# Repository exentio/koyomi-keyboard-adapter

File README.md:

# Project Koyomi - keyboard adapter boards

Adapter boards for the Vaio P keyboard, made from the reverse engineering for
Project Koyomi, read [this blog post](https://blog.exentio.sexy/2024/04/25/project-koyomi-update-2.html)
for more.  
Consider these reference designs, you can use them in hand-wired builds, to
test other keyboard variations, or for use in your own projects!  

**⚠️ WARNING: at the moment of writing, the boards haven't been tested.**  
**I'm also planning a major redesign using the RP2354B.**

The boards come in two variants, one with the RP2040 running the QMK firmware,
and another using the RP2354A with currently no firmware (waiting for QMK
support).  
For the RP2040 board, you can find the necessary build files in the
`qmk-firmware` folder. Once the board is made and tested and all the features 
are added (the extra keys are missing), it'll be pushed to the mainstream QMK
repo.  
The only supported layout for now is the JIS (Japanese) one on the first gen
Vaio P, but it's merely a matter of reversing the matrix and changing the pins
and layouts in the QMK config as necessary.  

Since the adapter's only concern is the keyboard, a header breaks out the
following:  
+ Lid detection sensor
+ Power switch
+ Power LED
+ Charging LED
+ Standby LED
+ WiFi switch
+ WiFi LED
+ Disk activity LED
+ Scroll lock LED (due to lack of GPIOs)

The keyboard connector is made by Panasonic, and the model number is
`AXK750147G`, bear in mind that the connector can connect in both ways, check
the GND connections marked on the board, the darkest traces on the keyboard
connector lead to GND.  

---

### Forking guidelines
I hope that this design will inspire people to work on similar projects, and
that they'll be used as references to learn how to work on similar projects!  
If you want to make any contribution, you're welcome to fork and send a pull
request, as long as LLMs are not directly involved and you understand your
changes: please refer to (HUMAN.md)[https://github.com/exentio/koyomi-hdmi-lvds/blob/main/HUMAN.md], thank you.  

You're also welcome to make changes to any part of this project to implement
different design choices, without having to send a pull request; however, if
your fork takes a completely different direction from Koyomi and breaks
compatibility, I kindly ask you to drop the name "Koyomi" from your project.
Please also remove every art on the PCB, if possible (wouldn't make sense to
have my face on a completely different project anyway).  
This can't and won't be enforced, so I'm just asking informally to please
respect this request, if you want to use my designs.  

### Commercial use
I purposely decided to allow commercial use for this project for two reasons: I
would be happy if modernized Vaio Ps and Koyomi were to be used in professional
contexts, and to let people distribute PCBs so everyone can build their own,
without having to sell parts myself, which is not something I can handle.  

If you plan to sell boards and parts, I only have these simple requests:  
- Please make them reasonably affordable and don't mark them up absurdly, I
want this project to be approachable from every point of view.  
- If you're profiting from reselling my designs, please donate something back
to the people who made the designs you're selling.  
- Don't remove any drawings/art on the PCBs, but you're allowed to add your own.  

None of these can and will be enforced, so I'm just asking you to respect the
time and hard work the other contributors and I have poured into designing
Koyomi.

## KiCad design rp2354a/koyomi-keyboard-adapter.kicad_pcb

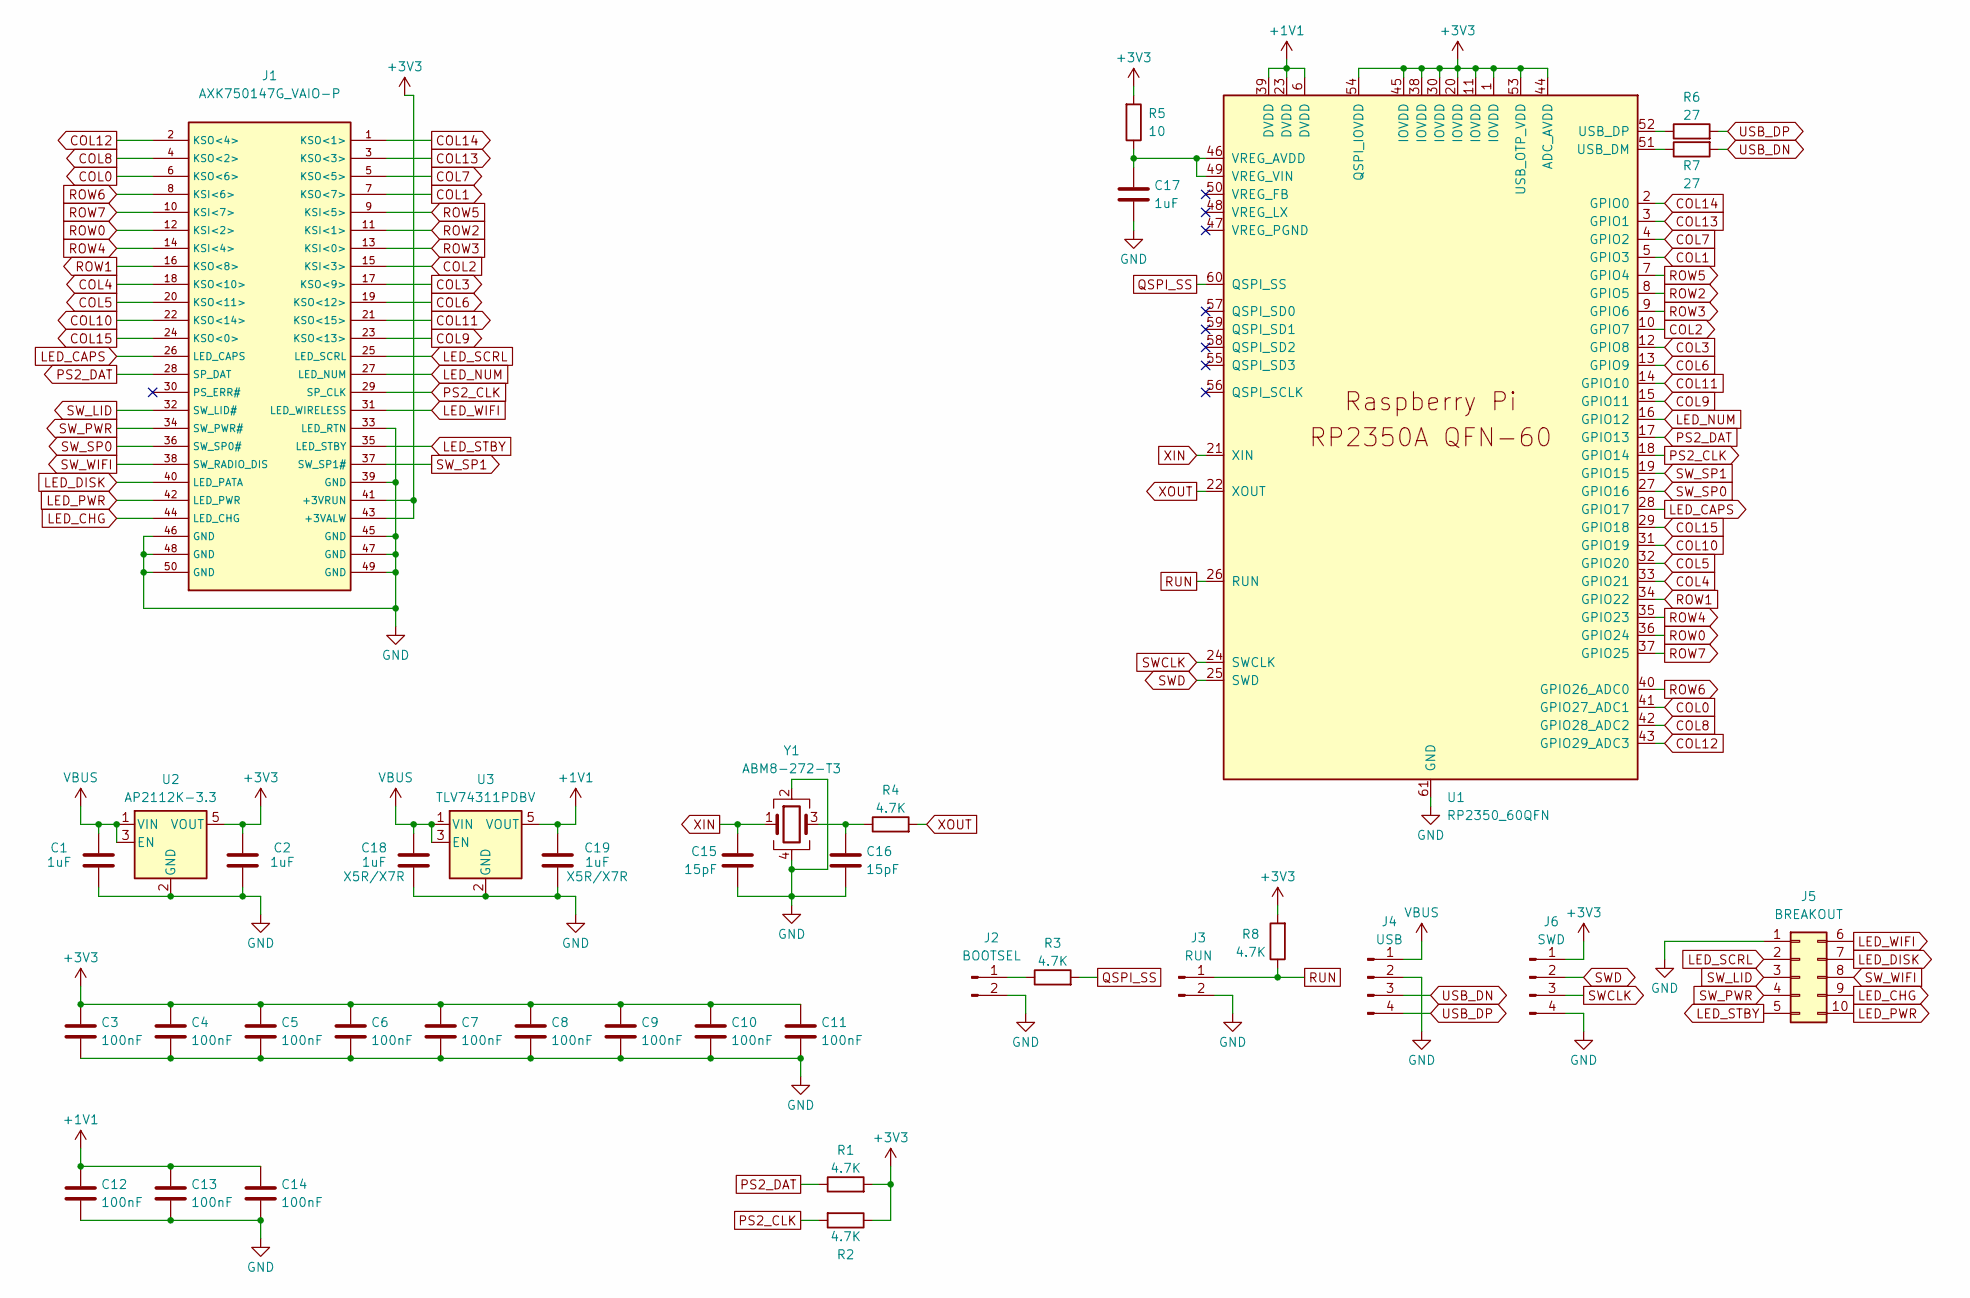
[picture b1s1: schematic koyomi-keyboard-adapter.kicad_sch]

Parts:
C1, C2, C17, C18, C19: 1uF; C_0402_1005Metric
C3, C4, C5, C6, C7, C8, C9, C10, C11, C12, C13, C14: 100nF; C_0402_1005Metric
C15, C16: 15pF; C_0402_1005Metric
J1: AXK750147G_VAIO-P
J2: BOOTSEL; PinHeader_1x02_P2.54mm_Vertical
J3: RUN; PinHeader_1x02_P2.54mm_Vertical
J4: USB; PinHeader_1x04_P2.54mm_Vertical
J5: BREAKOUT; PinHeader_2x05_P2.54mm_Vertical
J6: SWD; PinHeader_1x04_P2.54mm_Vertical
R1, R2, R3, R4, R8: 4.7K; R_0402_1005Metric
R5: 10; R_0402_1005Metric
R6, R7: 27; R_0402_1005Metric
U1: RP2350_60QFN; MCU_RaspberryPi_RP2350
U2: AP2112K-3.3; SOT-23-5
U3: TLV74311PDBV; SOT-23-5
Y1: ABM8-272-T3; Crystal_SMD_3225-4Pin_3.2x2.5mm

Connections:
+1V1: C12.1, C13.1, C14.1, C19.1, U1.6 (DVDD), U1.23 (DVDD), U1.39 (DVDD), U3.5 (VOUT)
+3V3: C2.1, C3.1, C4.1, C5.1, C6.1, C7.1, C8.1, C9.1, C10.1, C11.1, J1.41 (+3VRUN), J1.43 (+3VALW), J6.1, R1.2, R2.1, R5.2, R8.2, U1.1 (IOVDD), U1.11 (IOVDD), U1.20 (IOVDD), U1.30 (IOVDD), U1.38 (IOVDD), U1.44 (ADC_AVDD), U1.45 (IOVDD), U1.53 (USB_OTP_VDD), U1.54 (QSPI_IOVDD), U2.5 (VOUT); also elsewhere on the board
COL0: J1.6 (KSO<6>), U1.41 (GPIO27_ADC1)
COL1: J1.7 (KSO<7>), U1.5 (GPIO3)
COL2: J1.15 (KSI<3>), U1.10 (GPIO7)
COL3: J1.17 (KSO<9>), U1.12 (GPIO8)
COL4: J1.18 (KSO<10>), U1.33 (GPIO21)
COL5: J1.20 (KSO<11>), U1.32 (GPIO20)
COL6: J1.19 (KSO<12>), U1.13 (GPIO9)
COL7: J1.5 (KSO<5>), U1.4 (GPIO2)
COL8: J1.4 (KSO<2>), U1.42 (GPIO28_ADC2)
COL9: J1.23 (KSO<13>), U1.15 (GPIO11)
COL10: J1.22 (KSO<14>), U1.31 (GPIO19)
COL11: J1.21 (KSO<15>), U1.14 (GPIO10)
COL12: J1.2 (KSO<4>), U1.43 (GPIO29_ADC3)
COL13: J1.3 (KSO<3>), U1.3 (GPIO1)
COL14: J1.1 (KSO<1>), U1.2 (GPIO0)
COL15: J1.24 (KSO<0>), U1.29 (GPIO18)
GND: C1.2, C2.2, C3.2, C4.2, C5.2, C6.2, C7.2, C8.2, C9.2, C10.2, C11.2, C12.2, C13.2, C14.2, C15.2, C16.2, C17.2, C18.2, C19.2, J1.33 (LED_RTN), J1.39 (GND), J1.45 (GND), J1.46 (GND), J1.47 (GND), J1.48 (GND), J1.49 (GND), J1.50 (GND), J2.2, J3.2, J4.2, J5.1, J6.4, U1.61 (GND), U2.2 (GND), U3.2 (GND), Y1.2, Y1.4; also elsewhere on the board
LED_CAPS: J1.26 (LED_CAPS), U1.28 (GPIO17)
LED_CHG: J1.44 (LED_CHG), J5.9
LED_DISK: J1.40 (LED_PATA), J5.7
LED_NUM: J1.27 (LED_NUM), U1.16 (GPIO12)
LED_PWR: J1.42 (LED_PWR), J5.10
LED_SCRL: J1.25 (LED_SCRL), J5.2
LED_STBY: J1.35 (LED_STBY), J5.5
LED_WIFI: J1.31 (LED_WIRELESS), J5.6
unnamed: C16.1, R4.1, Y1.3
unnamed: J2.1, R3.1
unnamed: R7.1, U1.51 (USB_DM)
unnamed: R6.1, U1.52 (USB_DP)
unnamed: C17.1, R5.1, U1.46 (VREG_AVDD), U1.49 (VREG_VIN)
PS2_CLK: J1.29 (SP_CLK), R2.2, U1.18 (GPIO14)
PS2_DAT: J1.28 (SP_DAT), R1.1, U1.17 (GPIO13)
QSPI_SS: R3.2, U1.60 (QSPI_SS)
ROW0: J1.12 (KSI<2>), U1.36 (GPIO24)
ROW1: J1.16 (KSO<8>), U1.34 (GPIO22)
ROW2: J1.11 (KSI<1>), U1.8 (GPIO5)
ROW3: J1.13 (KSI<0>), U1.9 (GPIO6)
ROW4: J1.14 (KSI<4>), U1.35 (GPIO23)
ROW5: J1.9 (KSI<5>), U1.7 (GPIO4)
ROW6: J1.8 (KSI<6>), U1.40 (GPIO26_ADC0)
ROW7: J1.10 (KSI<7>), U1.37 (GPIO25)
RUN: J3.1, R8.1, U1.26 (RUN)
SWCLK: J6.3, U1.24 (SWCLK)
SWD: J6.2, U1.25 (SWD)
SW_LID: J1.32 (SW_LID#), J5.3
SW_PWR: J1.34 (SW_PWR#), J5.4
SW_SP0: J1.36 (SW_SP0#), U1.27 (GPIO16)
SW_SP1: J1.37 (SW_SP1#), U1.19 (GPIO15)
SW_WIFI: J1.38 (SW_RADIO_DIS), J5.8
USB_DN: J4.3, R7.2
USB_DP: J4.4, R6.2
VBUS: C1.1, C18.1, J4.1, U2.1 (VIN), U2.3 (EN), U3.1 (VIN), U3.3 (EN)
XIN: C15.1, U1.21 (XIN), Y1.1
XOUT: R4.2, U1.22 (XOUT)

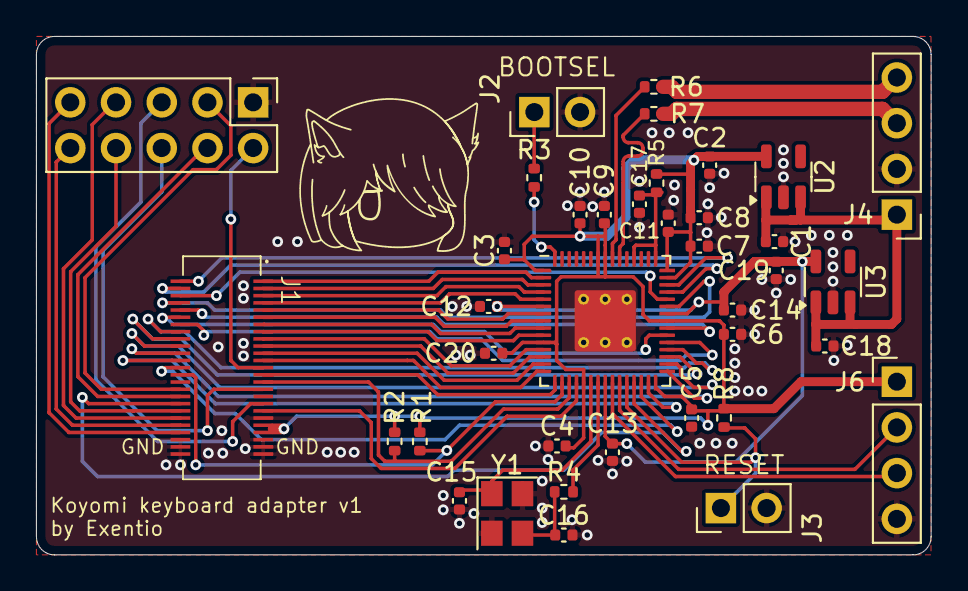
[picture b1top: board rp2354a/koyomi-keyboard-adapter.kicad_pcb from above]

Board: 2 copper layers, 49.7 x 28.8 mm, 38 parts (0 on the bottom side), 56 nets.

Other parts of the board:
C20: 100nF; C_0402_1005Metric

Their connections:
+3V3: C20.1; also elsewhere on the board
GND: C20.2; also elsewhere on the board

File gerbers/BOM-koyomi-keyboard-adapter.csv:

Comment,Designator,Footprint,LCSC
15pF,"C16,C17",C_0402_1005Metric,C1548
100nF,"C10,C12,C13,C15,C3,C4,C5,C6,C7,C8,C9",C_0402_1005Metric,C1591
1uF,"C1,C11,C14,C2",C_0402_1005Metric,C1592
RP2040,U1,QFN-56-1EP_7x7mm_P0.4mm_EP3.2x3.2mm,C2040
ABM8-272-T3,Y1,Crystal_SMD_3225-4Pin_3.2x2.5mm,C20625731
27,"R5,R6",R_0402_1005Metric,C25100
AP2112K-3.3,U2,SOT-23-5,C51118
4.7K,"R1,R2,R3,R4,R7",R_0402_1005Metric,C844791
W25Q128JVS,U3,SOIC-8_5.23x5.23mm_P1.27mm,C97521

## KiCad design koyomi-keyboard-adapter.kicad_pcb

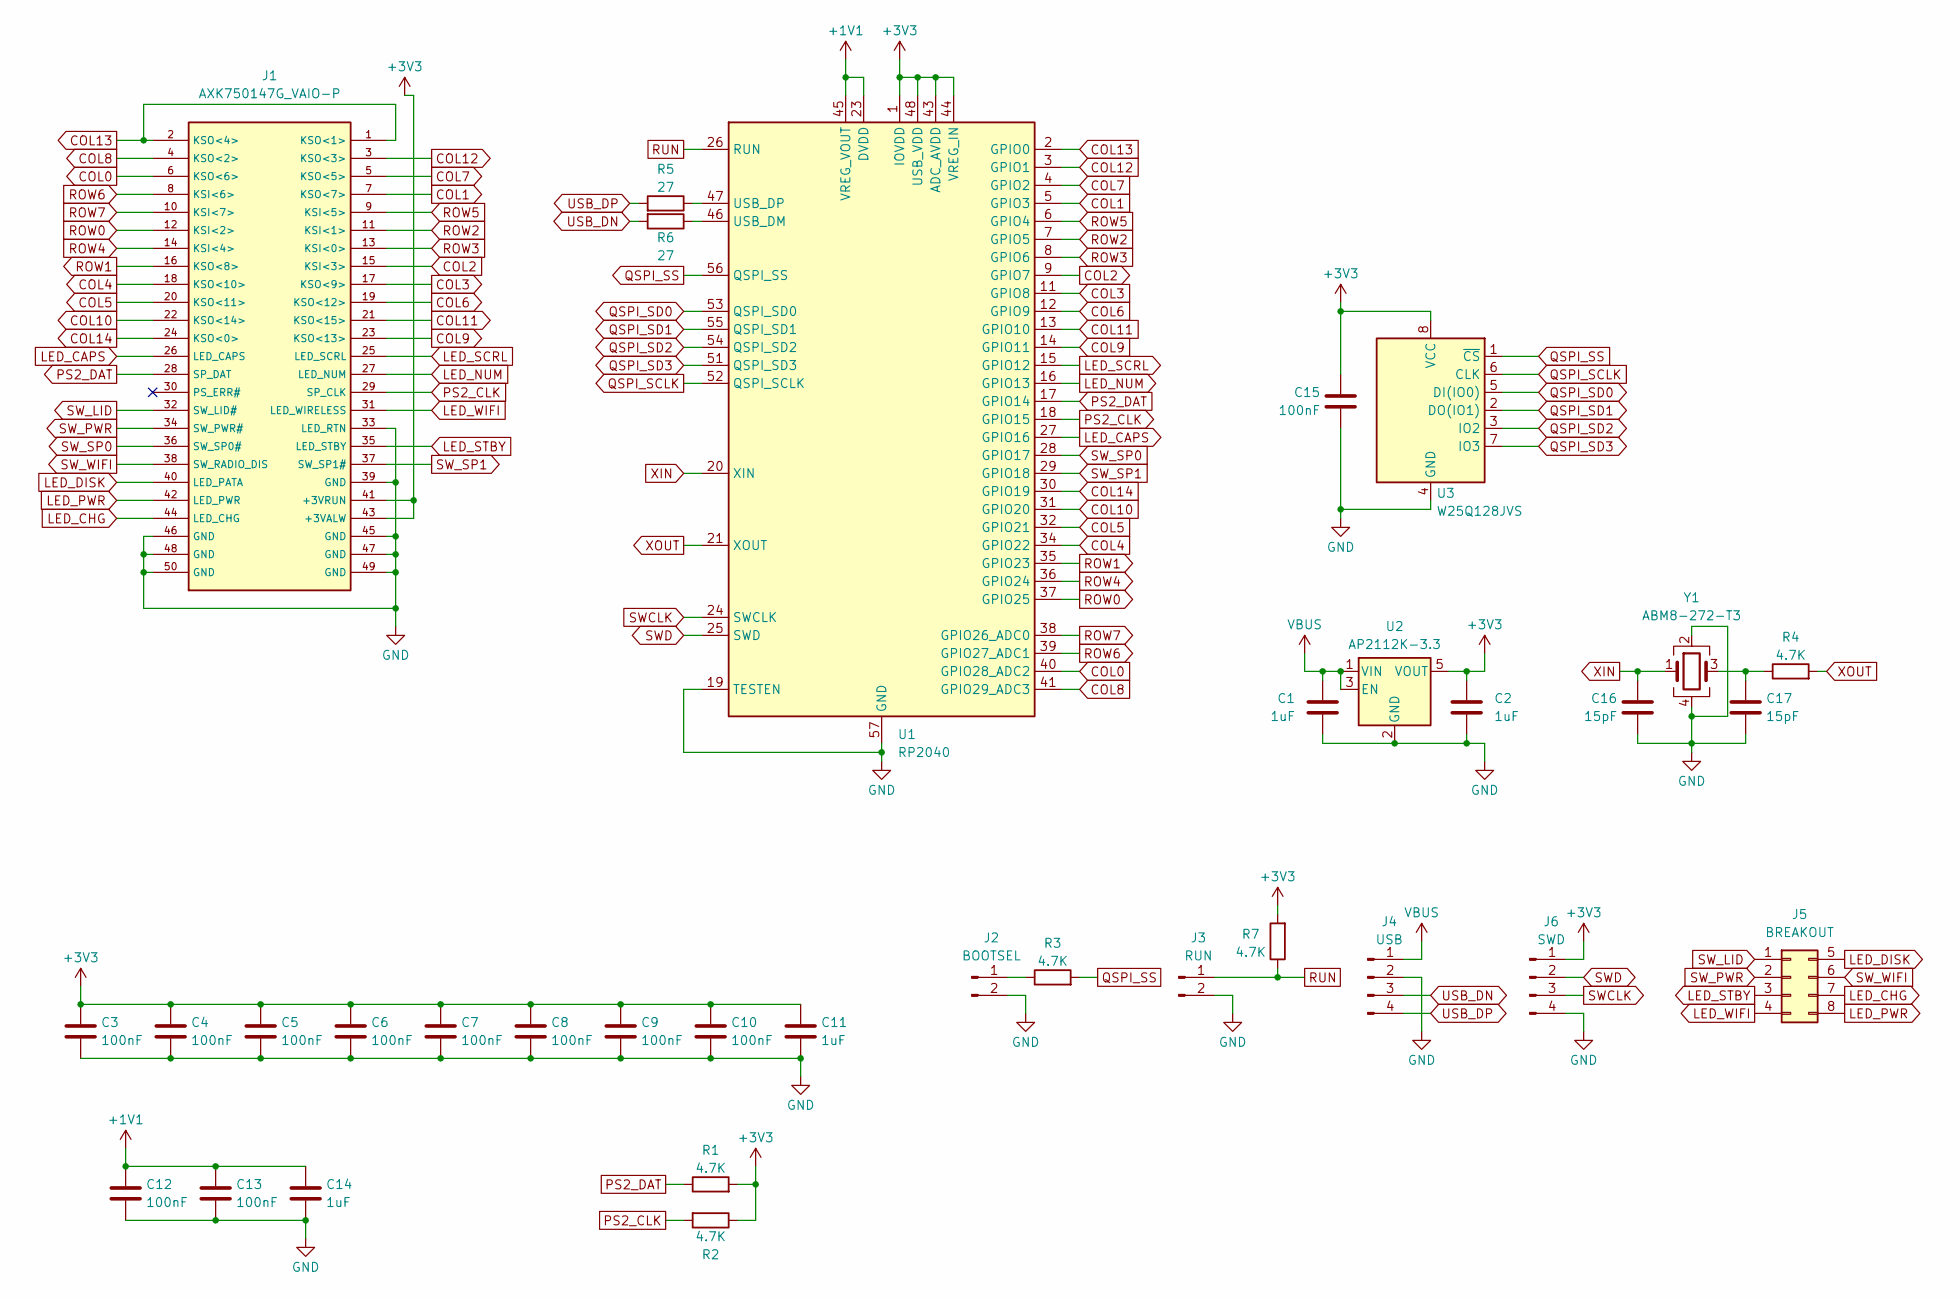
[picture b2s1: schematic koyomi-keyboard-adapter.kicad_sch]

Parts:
C1, C2, C11, C14: 1uF; C_0402_1005Metric
C3, C4, C5, C6, C7, C8, C9, C10, C12, C13, C15: 100nF; C_0402_1005Metric
C16, C17: 15pF; C_0402_1005Metric
J1: AXK750147G_VAIO-P
J2: BOOTSEL; PinHeader_1x02_P2.54mm_Vertical
J3: RUN; PinHeader_1x02_P2.54mm_Vertical
J4: USB; PinHeader_1x04_P2.54mm_Vertical
J5: BREAKOUT; PinHeader_2x04_P2.54mm_Vertical
J6: SWD; PinHeader_1x04_P2.54mm_Vertical
R1, R2, R3, R4, R7: 4.7K; R_0402_1005Metric
R5, R6: 27; R_0402_1005Metric
U1: RP2040; QFN-56-1EP_7x7mm_P0.4mm_EP3.2x3.2mm
U2: AP2112K-3.3; SOT-23-5
U3: W25Q128JVS; SOIC-8_5.23x5.23mm_P1.27mm
Y1: ABM8-272-T3; Crystal_SMD_3225-4Pin_3.2x2.5mm

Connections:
+1V1: C12.1, C13.1, C14.1, U1.23 (DVDD), U1.45 (VREG_VOUT), U1.50 (DVDD)
+3V3: C2.1, C3.1, C4.1, C5.1, C6.1, C7.1, C8.1, C9.1, C10.1, C11.1, C15.1, J1.41 (+3VRUN), J1.43 (+3VALW), J6.1, R1.2, R2.1, R7.2, U1.1 (IOVDD), U1.10 (IOVDD), U1.22 (IOVDD), U1.33 (IOVDD), U1.42 (IOVDD), U1.43 (ADC_AVDD), U1.44 (VREG_IN), U1.48 (USB_VDD), U1.49 (IOVDD), U2.5 (VOUT), U3.8 (VCC)
COL0: J1.6 (KSO<6>), U1.40 (GPIO28_ADC2)
COL1: J1.7 (KSO<7>), U1.5 (GPIO3)
COL2: J1.15 (KSI<3>), U1.9 (GPIO7)
COL3: J1.17 (KSO<9>), U1.11 (GPIO8)
COL4: J1.18 (KSO<10>), U1.34 (GPIO22)
COL5: J1.20 (KSO<11>), U1.32 (GPIO21)
COL6: J1.19 (KSO<12>), U1.12 (GPIO9)
COL7: J1.5 (KSO<5>), U1.4 (GPIO2)
COL8: J1.4 (KSO<2>), U1.41 (GPIO29_ADC3)
COL9: J1.23 (KSO<13>), U1.14 (GPIO11)
COL10: J1.22 (KSO<14>), U1.31 (GPIO20)
COL11: J1.21 (KSO<15>), U1.13 (GPIO10)
COL12: J1.3 (KSO<3>), U1.3 (GPIO1)
COL13: J1.1 (KSO<1>), J1.2 (KSO<4>), U1.2 (GPIO0)
COL14: J1.24 (KSO<0>), U1.30 (GPIO19)
GND: C1.2, C2.2, C3.2, C4.2, C5.2, C6.2, C7.2, C8.2, C9.2, C10.2, C11.2, C12.2, C13.2, C14.2, C15.2, C16.2, C17.2, J1.33 (LED_RTN), J1.39 (GND), J1.45 (GND), J1.46 (GND), J1.47 (GND), J1.48 (GND), J1.49 (GND), J1.50 (GND), J2.2, J3.2, J4.2, J6.4, U1.19 (TESTEN), U1.57 (GND), U2.2 (GND), U3.4 (GND), Y1.2, Y1.4
LED_CAPS: J1.26 (LED_CAPS), U1.27 (GPIO16)
LED_CHG: J1.44 (LED_CHG), J5.7
LED_DISK: J1.40 (LED_PATA), J5.5
LED_NUM: J1.27 (LED_NUM), U1.16 (GPIO13)
LED_PWR: J1.42 (LED_PWR), J5.8
LED_SCRL: J1.25 (LED_SCRL), U1.15 (GPIO12)
LED_STBY: J1.35 (LED_STBY), J5.3
LED_WIFI: J1.31 (LED_WIRELESS), J5.4
unnamed: C17.1, R4.1, Y1.3
unnamed: J2.1, R3.1
unnamed: R6.1, U1.46 (USB_DM)
unnamed: R5.1, U1.47 (USB_DP)
PS2_CLK: J1.29 (SP_CLK), R2.2, U1.18 (GPIO15)
PS2_DAT: J1.28 (SP_DAT), R1.1, U1.17 (GPIO14)
QSPI_SCLK: U1.52 (QSPI_SCLK), U3.6 (CLK)
QSPI_SD0: U1.53 (QSPI_SD0), U3.5 (DI(IO0))
QSPI_SD1: U1.55 (QSPI_SD1), U3.2 (DO(IO1))
QSPI_SD2: U1.54 (QSPI_SD2), U3.3 (IO2)
QSPI_SD3: U1.51 (QSPI_SD3), U3.7 (IO3)
QSPI_SS: R3.2, U1.56 (QSPI_SS), U3.1 (~CS)
ROW0: J1.12 (KSI<2>), U1.37 (GPIO25)
ROW1: J1.16 (KSO<8>), U1.35 (GPIO23)
ROW2: J1.11 (KSI<1>), U1.7 (GPIO5)
ROW3: J1.13 (KSI<0>), U1.8 (GPIO6)
ROW4: J1.14 (KSI<4>), U1.36 (GPIO24)
ROW5: J1.9 (KSI<5>), U1.6 (GPIO4)
ROW6: J1.8 (KSI<6>), U1.39 (GPIO27_ADC1)
ROW7: J1.10 (KSI<7>), U1.38 (GPIO26_ADC0)
RUN: J3.1, R7.1, U1.26 (RUN)
SWCLK: J6.3, U1.24 (SWCLK)
SWD: J6.2, U1.25 (SWD)
SW_LID: J1.32 (SW_LID#), J5.1
SW_PWR: J1.34 (SW_PWR#), J5.2
SW_SP0: J1.36 (SW_SP0#), U1.28 (GPIO17)
SW_SP1: J1.37 (SW_SP1#), U1.29 (GPIO18)
SW_WIFI: J1.38 (SW_RADIO_DIS), J5.6
USB_DN: J4.3, R6.2
USB_DP: J4.4, R5.2
VBUS: C1.1, J4.1, U2.1 (VIN), U2.3 (EN)
XIN: C16.1, U1.20 (XIN), Y1.1
XOUT: R4.2, U1.21 (XOUT)

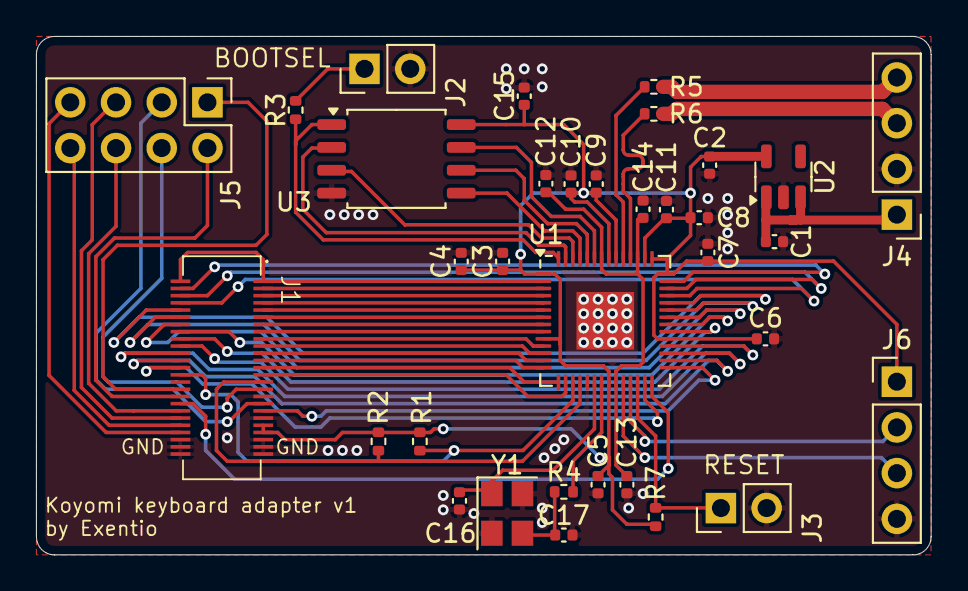
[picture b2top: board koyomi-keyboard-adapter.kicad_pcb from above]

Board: 2 copper layers, 49.7 x 28.8 mm, 34 parts (0 on the bottom side), 59 nets.

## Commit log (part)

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2024-05-15 Add license
2024-07-21 Gerbers and JLCPCB files update
2024-08-01 Changed PCB art to simple silkscreen lines
2024-08-03 Update gerbers to reflect recent changes
2024-09-19 Readme update, added ghosting to QMK config
2024-09-27 Decompressed matrix, broken out scroll lock LED, readme update
2024-10-03 RP2354A variant added, repo folder layout changed, readme update
2024-12-27 Fix JLCPCB rotations
